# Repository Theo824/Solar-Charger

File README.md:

Designed and built a solar panel-powered constant-current charger for NiMH or NiCD batteries, or an iPhone, 
which can function as a power bank or be used in other devices.

The voltages are adjustable to accommodate any battery, and the solar panels are detachable through screw connectors.

Conceived the design concept centred around only two transistors. 
Researched the iPhone charging handshake protocol, modified the circuit in NI Multisim to correct functionality, 
and integrated it onto a 2-layer PCB using KiCad.

The charger delivered 5 W to the iPhone and 4 W to five AA NiMH batteries in series.
Once fully charged, the auto-cutoff reduced the charging current by 85.12% to 0.025C. 

In theory, the batteries could also charge an iPhone 12 Pro Max up to three times without the solar panels.

The LED display shows the battery voltage. 
To turn it to iPhone charging, turn the switches down; for NiMH charging, turn them up.

For more step-by-step information on the process or log of making this project, please look at solarCharger24-25_Logbook.pdf or solarCharger24-25_Logbook.docx: [Click here to view the Cloud File](https://1drv.ms/w/c/10176ce2d1328c94/IQDAm-Wb3D2zQ42p3uI7dwKKAQNEjcbpd-CYOFzZ3OIuXmA?e=BsMwEE)

Note: The descriptions are below their corresponding images.

The PCB could be made significantly smaller by using smaller components, switching to surface-mount devices, 
and removing test components such as screw connectors. 

I did not use surface-mount devices because my inexpensive soldering kit cannot solder them precisely. 
Using only one buck converter is not feasible, since a 5 V output cannot charge 5 × AA NiMH batteries (5–7 V), 
lower battery voltages cannot charge an iPhone, and using more than 5 V with a single buck converter would damage the iPhone.

If you look closely, you can see the iPhone lightning symbol, which indicates charging. 
The power adapter could not give more than 0.53 A.

The graph above is the data gathered from testing the breadboard prototype on charging NiMH battery.
It indicates auto-cutoff at 7.25 V or 1.45 V each battery cell.

0.48 A is the charging current of the NiMH battery.

The graph above is the data gathered from testing the PCB prototype on charging NiMH battery. 
It indicates auto-cutoff at 7.33 V or 1.466 V each battery cell.

0.83 A is the recorded charging current of iPhone. This fluctuated around 1 A (5 W) throughout the testing.

The graph above illustrates the charging speed in relation to the battery percentage. It roughly takes 5 minutes to increase it by 1%.

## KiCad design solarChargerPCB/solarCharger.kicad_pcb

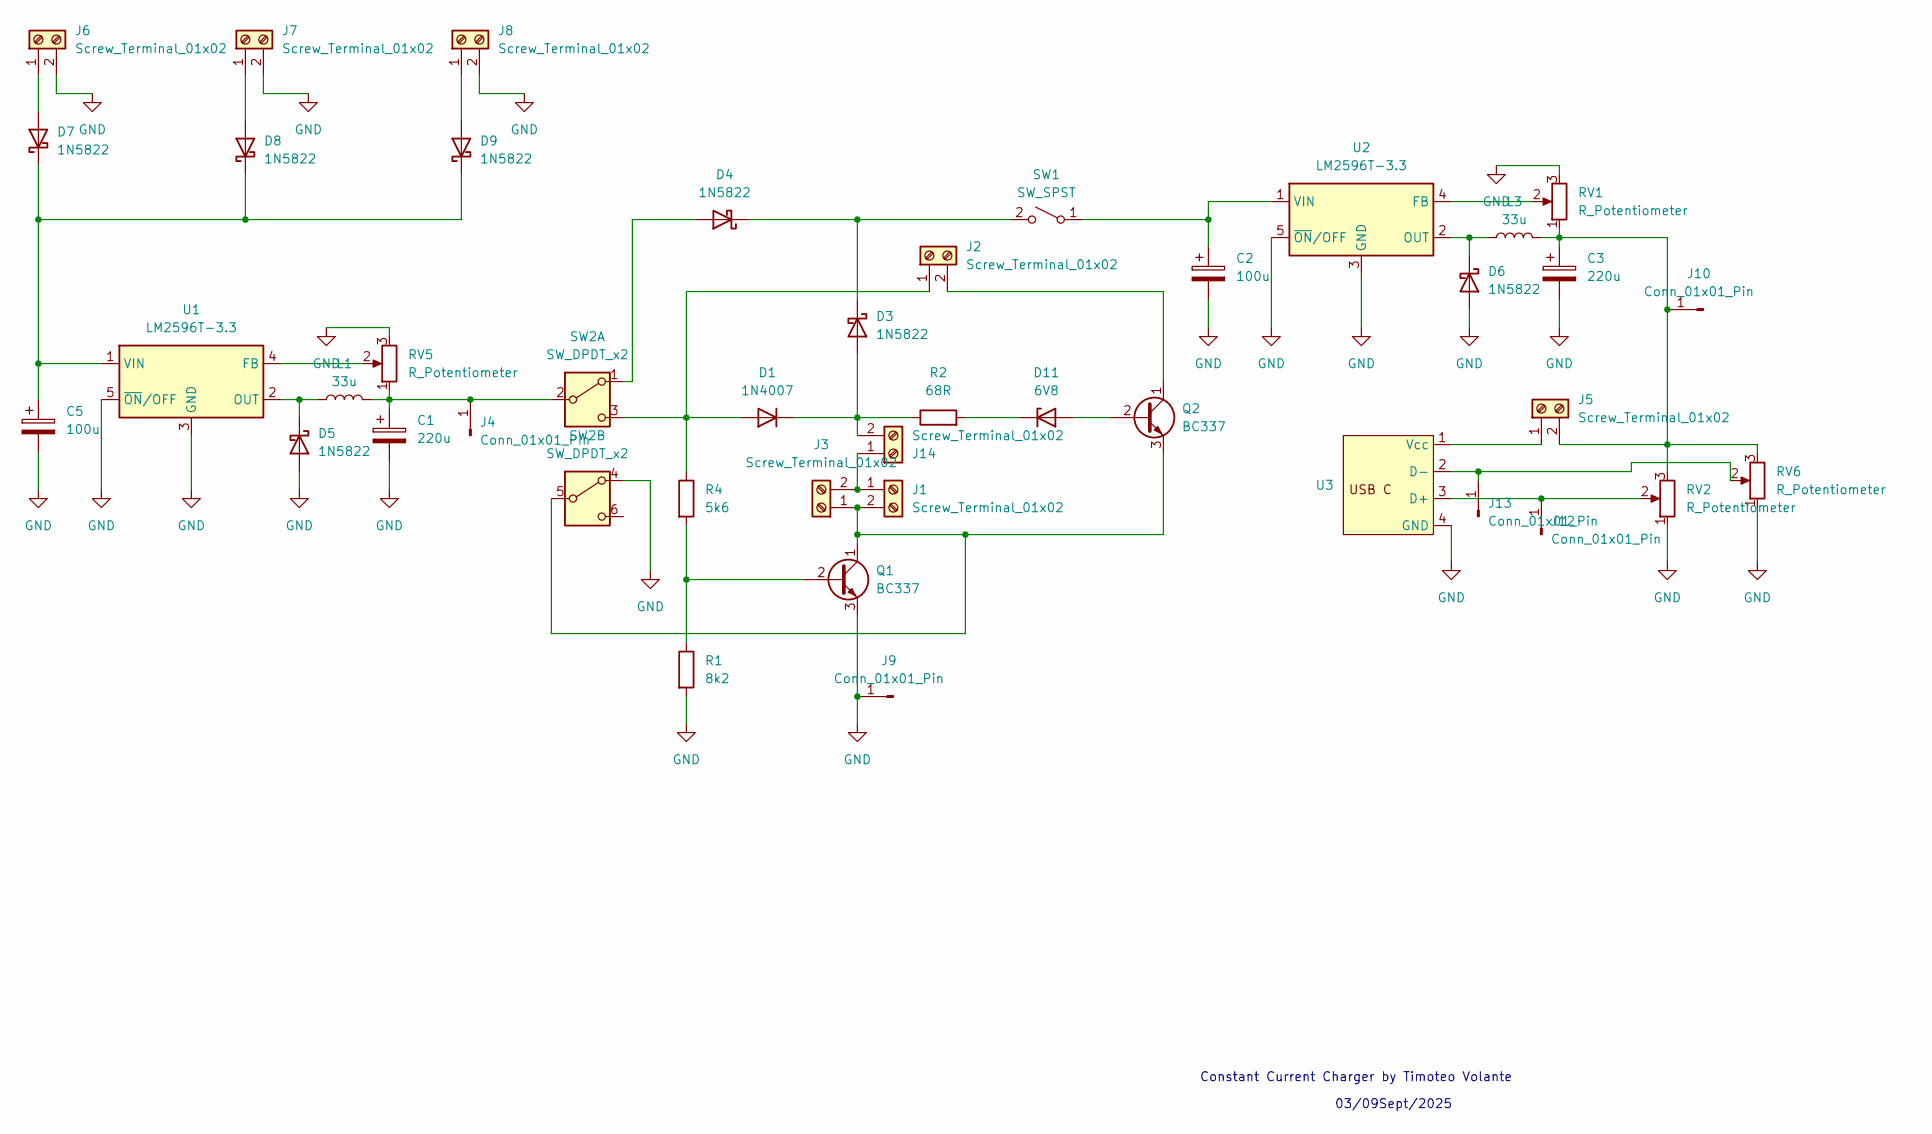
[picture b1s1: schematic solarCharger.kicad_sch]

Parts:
C1, C3: 220u; CP_Radial_D10.0mm_P5.00mm
C2, C5: 100u; CP_Radial_D8.0mm_P3.50mm
D1: 1N4007; D_DO-41_SOD81_P10.16mm_Horizontal
D3, D4, D5, D6, D7, D8, D9: 1N5822; D_DO-201AD_P15.24mm_Horizontal
D11: 6V8; D_DO-41_SOD81_P12.70mm_Horizontal
J1, J2, J3, J5, J6, J7, J8, J14: Screw_Terminal_01x02; 2_54mm_Pitch_Mount_Screw_Terminal_Connector
J4, J9, J10, J12, J13: Conn_01x01_Pin; PinHeader_1x01_P2.54mm_Vertical
L1, L3: 33u; inductor_L6mm_D2_3mm_W28mm
Q1, Q2: BC337; TO-92_Inline
R1: 8k2; R_Axial_DIN0207_L6.3mm_D2.5mm_P10.16mm_Horizontal
R2: 68R; R_Axial_DIN0207_L6.3mm_D2.5mm_P10.16mm_Horizontal
R4: 5k6; R_Axial_DIN0207_L6.3mm_D2.5mm_P10.16mm_Horizontal
RV1, RV2, RV5, RV6: R_Potentiometer; Potentiometer_Bourns_3296W_Vertical
SW1: SW_SPST; Toggle_SPST
SW2: SW_DPDT_x2; Toggle_DPDT
U1, U2: LM2596T-3.3; TO-220-5_P3.4x3.7mm_StaggerOdd_Lead3.8mm_Vertical
U3: USB_C_module

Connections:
GND: C1.2, C2.2, C3.2, C5.2, D5.2 (A), D6.2 (A), J6.2, J7.2, J8.2, J9.1, Q1.3 (E), R1.2, RV1.3, RV2.1, RV5.3, RV6.1, SW2.4 (A), U1.3 (GND), U1.5 (~ON/OFF), U2.3 (GND), U2.5 (~ON/OFF), U3.4 (GND)
unnamed: D1.2 (A), J2.1, R4.1, SW2.3 (C)
unnamed: D1.1 (K), D3.2 (A), J14.2, R2.1
unnamed: D3.1 (K), D4.1 (K), SW1.2 (B)
unnamed: D4.2 (A), SW2.1 (A)
unnamed: D5.1 (K), L1.1, U1.2 (OUT)
unnamed: D6.1 (K), L3.1, U2.2 (OUT)
unnamed: D7.2 (A), J6.1
unnamed: C5.1, D7.1 (K), D8.1 (K), D9.1 (K), U1.1 (VIN)
unnamed: D8.2 (A), J7.1
unnamed: D9.2 (A), J8.1
unnamed: D11.2 (A), Q2.2 (B)
unnamed: D11.1 (K), R2.2
unnamed: J1.1, J3.2, J14.1
unnamed: J1.2, J3.1, Q1.1 (C), Q2.3 (E), SW2.5 (B)
unnamed: J2.2, Q2.1 (C)
unnamed: C1.1, J4.1, L1.2, RV5.1, SW2.2 (B)
unnamed: J5.1, U3.1 (Vcc)
unnamed: C3.1, J5.2, J10.1, L3.2, RV1.1, RV2.3, RV6.3
unnamed: J12.1, RV2.2, U3.3 (D+)
unnamed: J13.1, RV6.2, U3.2 (D-)
unnamed: Q1.2 (B), R1.1, R4.2
unnamed: C2.1, SW1.1 (A), U2.1 (VIN)
unnamed: RV5.2, U1.4 (FB)
unnamed: RV1.2, U2.4 (FB)

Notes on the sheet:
Constant Current Charger by Timoteo Volante
03/09Sept/2025

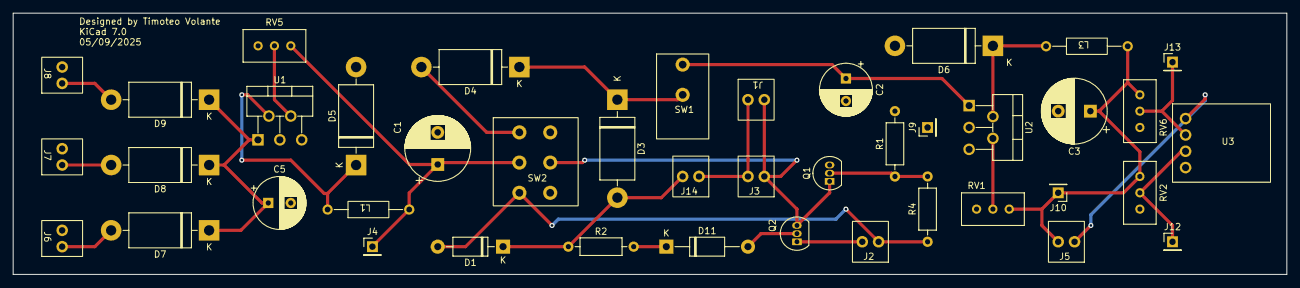
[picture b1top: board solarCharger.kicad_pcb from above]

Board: 2 copper layers, 198.1 x 40.6 mm, 42 parts (0 on the bottom side), 25 nets.
